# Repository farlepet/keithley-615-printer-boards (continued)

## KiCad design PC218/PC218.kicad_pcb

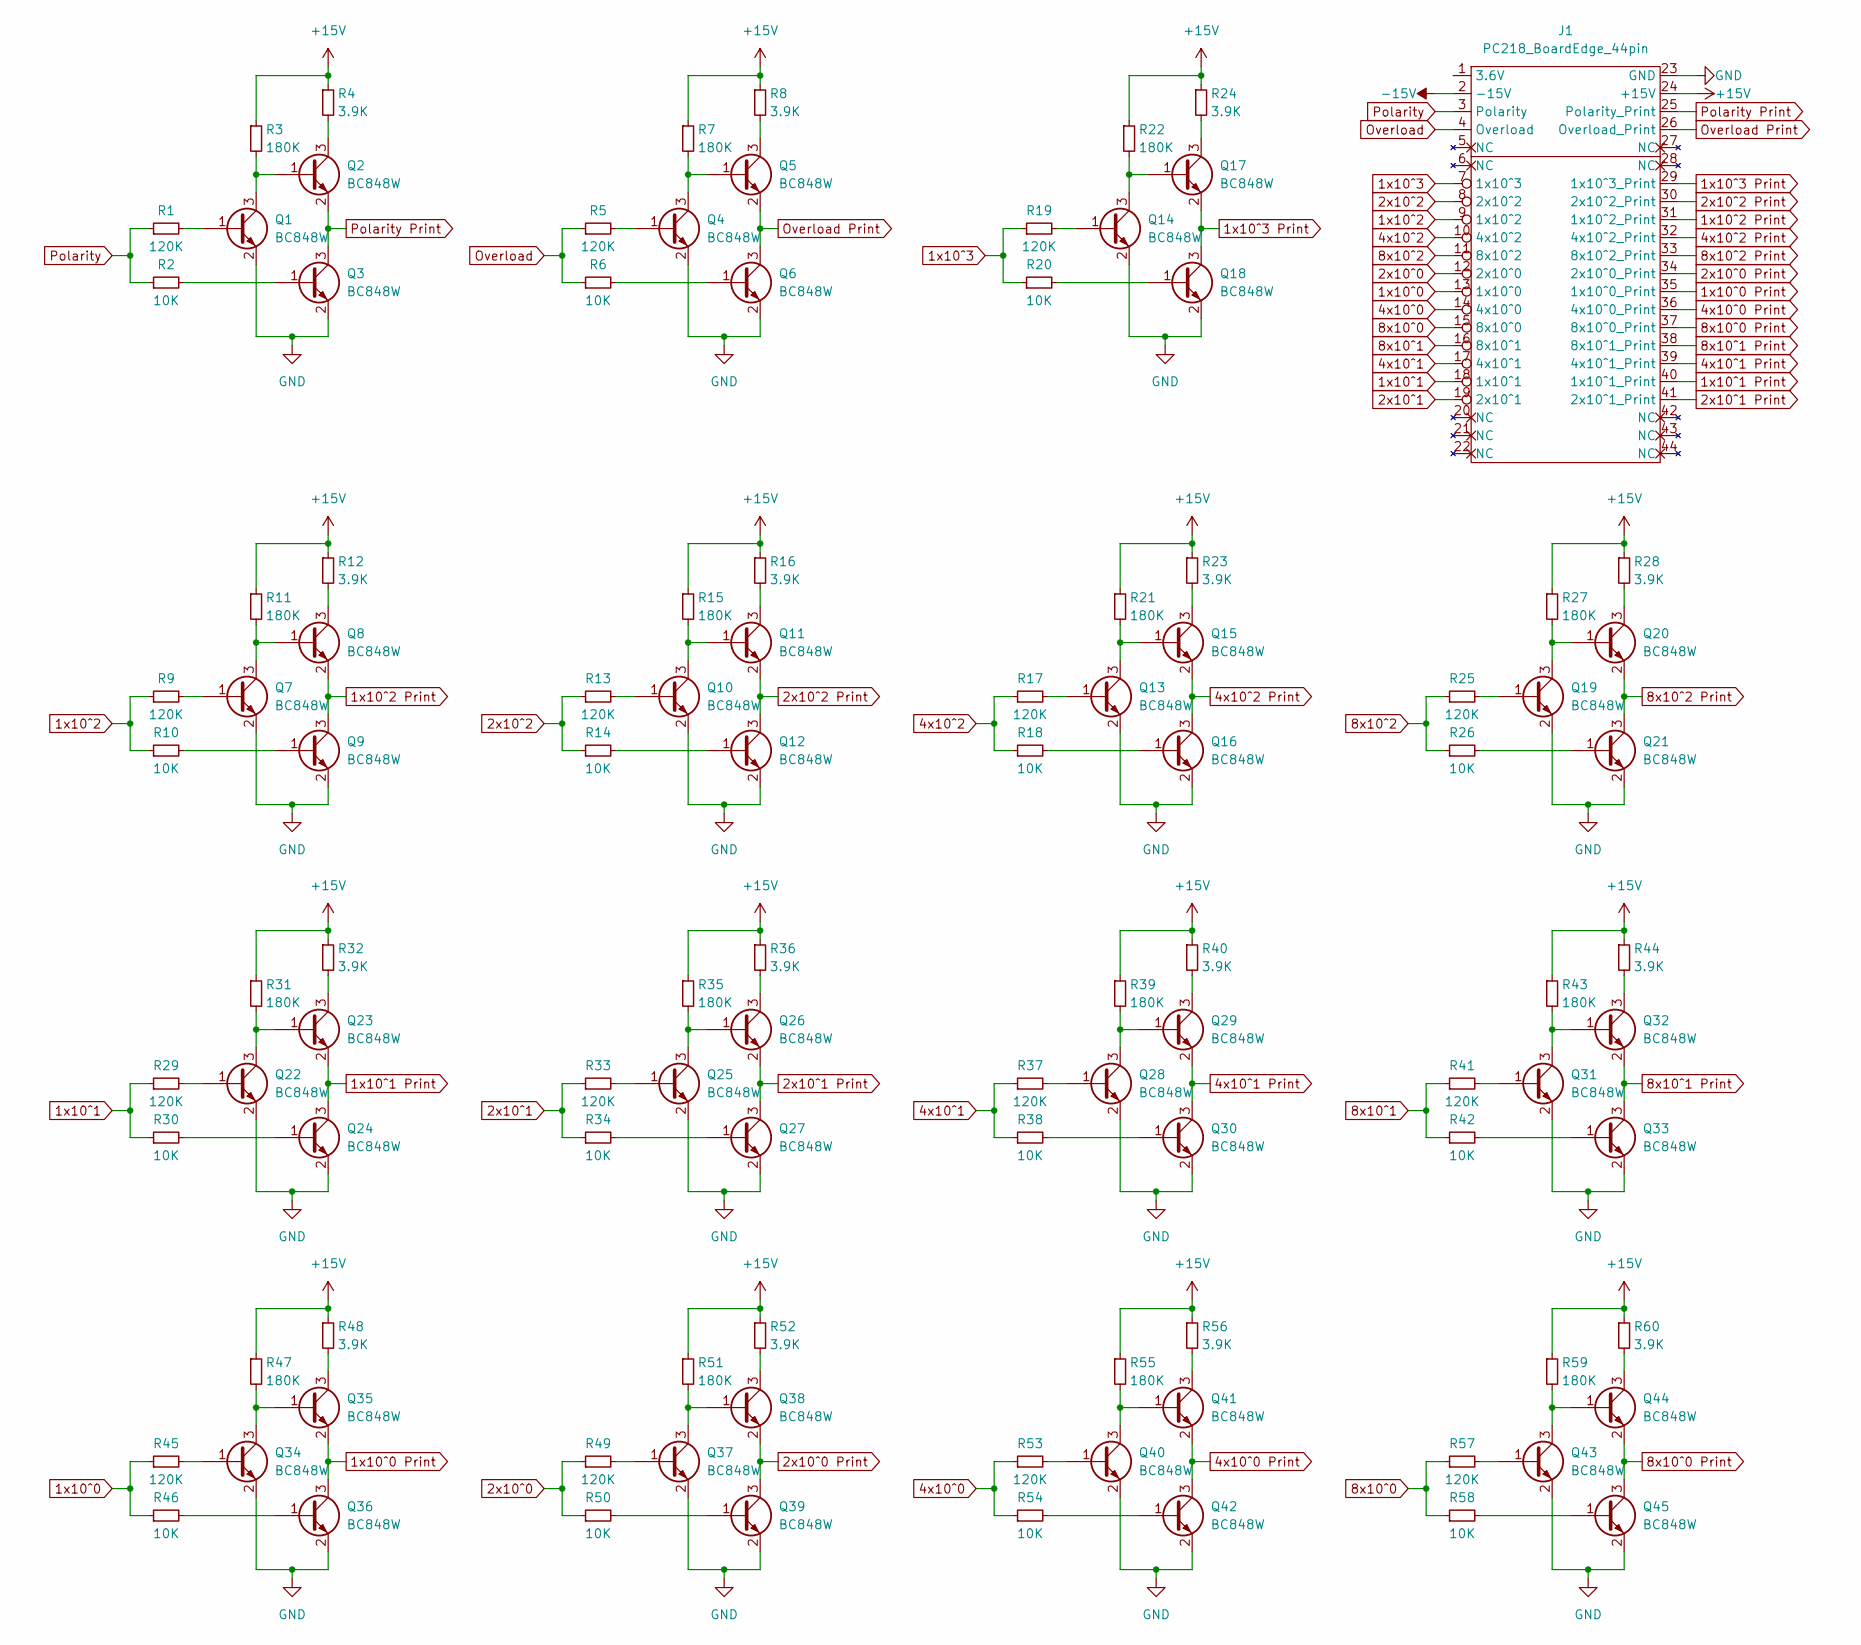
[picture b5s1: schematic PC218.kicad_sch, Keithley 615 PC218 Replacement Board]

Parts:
J1: PC218_BoardEdge_44pin; PC218_Edge_Connector
Q1, Q2, Q3, Q4, Q5, Q6, Q7, Q8, Q9, Q10, Q11, Q12, Q13, Q14, Q15, Q16, Q17, Q18, Q19, Q20, Q21, Q22, Q23, Q24, Q25, Q26, Q27, Q28, Q29, Q30, Q31, Q32, Q33, Q34, Q35, Q36, Q37, Q38, Q39, Q40, Q41, Q42, Q43, Q44, Q45: BC848W; SOT-323_SC-70
R1, R5, R9, R13, R17, R19, R25, R29, R33, R37, R41, R45, R49, R53, R57: 120K; R_0603_1608Metric
R2, R6, R10, R14, R18, R20, R26, R30, R34, R38, R42, R46, R50, R54, R58: 10K; R_0603_1608Metric
R3, R7, R11, R15, R21, R22, R27, R31, R35, R39, R43, R47, R51, R55, R59: 180K; R_0603_1608Metric
R4, R8, R12, R16, R23, R24, R28, R32, R36, R40, R44, R48, R52, R56, R60: 3.9K; R_0603_1608Metric

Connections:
1x10^0: J1.13 (1x10^0), R45.1, R46.1
1x10^0 Print: J1.35 (1x10^0_Print), Q35.2 (E), Q36.3 (C)
1x10^1: J1.18 (1x10^1), R29.1, R30.1
1x10^1 Print: J1.40 (1x10^1_Print), Q23.2 (E), Q24.3 (C)
1x10^2: J1.9 (1x10^2), R9.1, R10.1
1x10^2 Print: J1.31 (1x10^2_Print), Q8.2 (E), Q9.3 (C)
1x10^3: J1.7 (1x10^3), R19.1, R20.1
1x10^3 Print: J1.29 (1x10^3_Print), Q17.2 (E), Q18.3 (C)
2x10^0: J1.12 (2x10^0), R49.1, R50.1
2x10^0 Print: J1.34 (2x10^0_Print), Q38.2 (E), Q39.3 (C)
2x10^1: J1.19 (2x10^1), R33.1, R34.1
2x10^1 Print: J1.41 (2x10^1_Print), Q26.2 (E), Q27.3 (C)
2x10^2: J1.8 (2x10^2), R13.1, R14.1
2x10^2 Print: J1.30 (2x10^2_Print), Q11.2 (E), Q12.3 (C)
4x10^0: J1.14 (4x10^0), R53.1, R54.1
4x10^0 Print: J1.36 (4x10^0_Print), Q41.2 (E), Q42.3 (C)
4x10^1: J1.17 (4x10^1), R37.1, R38.1
4x10^1 Print: J1.39 (4x10^1_Print), Q29.2 (E), Q30.3 (C)
4x10^2: J1.10 (4x10^2), R17.1, R18.1
4x10^2 Print: J1.32 (4x10^2_Print), Q15.2 (E), Q16.3 (C)
8x10^0: J1.15 (8x10^0), R57.1, R58.1
8x10^0 Print: J1.37 (8x10^0_Print), Q44.2 (E), Q45.3 (C)
8x10^1: J1.16 (8x10^1), R41.1, R42.1
8x10^1 Print: J1.38 (8x10^1_Print), Q32.2 (E), Q33.3 (C)
8x10^2: J1.11 (8x10^2), R25.1, R26.1
8x10^2 Print: J1.33 (8x10^2_Print), Q20.2 (E), Q21.3 (C)
+15V: J1.24 (+15V), R3.1, R4.1, R7.1, R8.1, R11.1, R12.1, R15.1, R16.1, R21.1, R22.1, R23.1, R24.1, R27.1, R28.1, R31.1, R32.1, R35.1, R36.1, R39.1, R40.1, R43.1, R44.1, R47.1, R48.1, R51.1, R52.1, R55.1, R56.1, R59.1, R60.1
-15V: J1.2 (-15V)
GND: J1.23 (GND), Q1.2 (E), Q3.2 (E), Q4.2 (E), Q6.2 (E), Q7.2 (E), Q9.2 (E), Q10.2 (E), Q12.2 (E), Q13.2 (E), Q14.2 (E), Q16.2 (E), Q18.2 (E), Q19.2 (E), Q21.2 (E), Q22.2 (E), Q24.2 (E), Q25.2 (E), Q27.2 (E), Q28.2 (E), Q30.2 (E), Q31.2 (E), Q33.2 (E), Q34.2 (E), Q36.2 (E), Q37.2 (E), Q39.2 (E), Q40.2 (E), Q42.2 (E), Q43.2 (E), Q45.2 (E)
unnamed: Q1.1 (B), R1.2
unnamed: Q1.3 (C), Q2.1 (B), R3.2
unnamed: Q2.3 (C), R4.2
unnamed: Q3.1 (B), R2.2
unnamed: Q4.1 (B), R5.2
unnamed: Q4.3 (C), Q5.1 (B), R7.2
unnamed: Q5.3 (C), R8.2
unnamed: Q6.1 (B), R6.2
unnamed: Q7.1 (B), R9.2
unnamed: Q7.3 (C), Q8.1 (B), R11.2
unnamed: Q8.3 (C), R12.2
unnamed: Q9.1 (B), R10.2
unnamed: Q10.1 (B), R13.2
unnamed: Q10.3 (C), Q11.1 (B), R15.2
unnamed: Q11.3 (C), R16.2
unnamed: Q12.1 (B), R14.2
unnamed: Q13.1 (B), R17.2
unnamed: Q13.3 (C), Q15.1 (B), R21.2
unnamed: Q14.1 (B), R19.2
unnamed: Q14.3 (C), Q17.1 (B), R22.2
unnamed: Q15.3 (C), R23.2
unnamed: Q16.1 (B), R18.2
unnamed: Q17.3 (C), R24.2
unnamed: Q18.1 (B), R20.2
unnamed: Q19.1 (B), R25.2
unnamed: Q19.3 (C), Q20.1 (B), R27.2
unnamed: Q20.3 (C), R28.2
unnamed: Q21.1 (B), R26.2
unnamed: Q22.1 (B), R29.2
unnamed: Q22.3 (C), Q23.1 (B), R31.2
unnamed: Q23.3 (C), R32.2
unnamed: Q24.1 (B), R30.2
unnamed: Q25.1 (B), R33.2
unnamed: Q25.3 (C), Q26.1 (B), R35.2
unnamed: Q26.3 (C), R36.2
unnamed: Q27.1 (B), R34.2
unnamed: Q28.1 (B), R37.2
unnamed: Q28.3 (C), Q29.1 (B), R39.2
unnamed: Q29.3 (C), R40.2
unnamed: Q30.1 (B), R38.2
unnamed: Q31.1 (B), R41.2
unnamed: Q31.3 (C), Q32.1 (B), R43.2
unnamed: Q32.3 (C), R44.2
unnamed: Q33.1 (B), R42.2
unnamed: Q34.1 (B), R45.2
unnamed: Q34.3 (C), Q35.1 (B), R47.2
unnamed: Q35.3 (C), R48.2
unnamed: Q36.1 (B), R46.2
unnamed: Q37.1 (B), R49.2
unnamed: Q37.3 (C), Q38.1 (B), R51.2
unnamed: Q38.3 (C), R52.2
unnamed: Q39.1 (B), R50.2
unnamed: Q40.1 (B), R53.2
unnamed: Q40.3 (C), Q41.1 (B), R55.2
unnamed: Q41.3 (C), R56.2
unnamed: Q42.1 (B), R54.2
unnamed: Q43.1 (B), R57.2
unnamed: Q43.3 (C), Q44.1 (B), R59.2
unnamed: Q44.3 (C), R60.2
unnamed: Q45.1 (B), R58.2
Overload: J1.4 (Overload), R5.1, R6.1
Overload Print: J1.26 (Overload_Print), Q5.2 (E), Q6.3 (C)
Polarity: J1.3 (Polarity), R1.1, R2.1
Polarity Print: J1.25 (Polarity_Print), Q2.2 (E), Q3.3 (C)

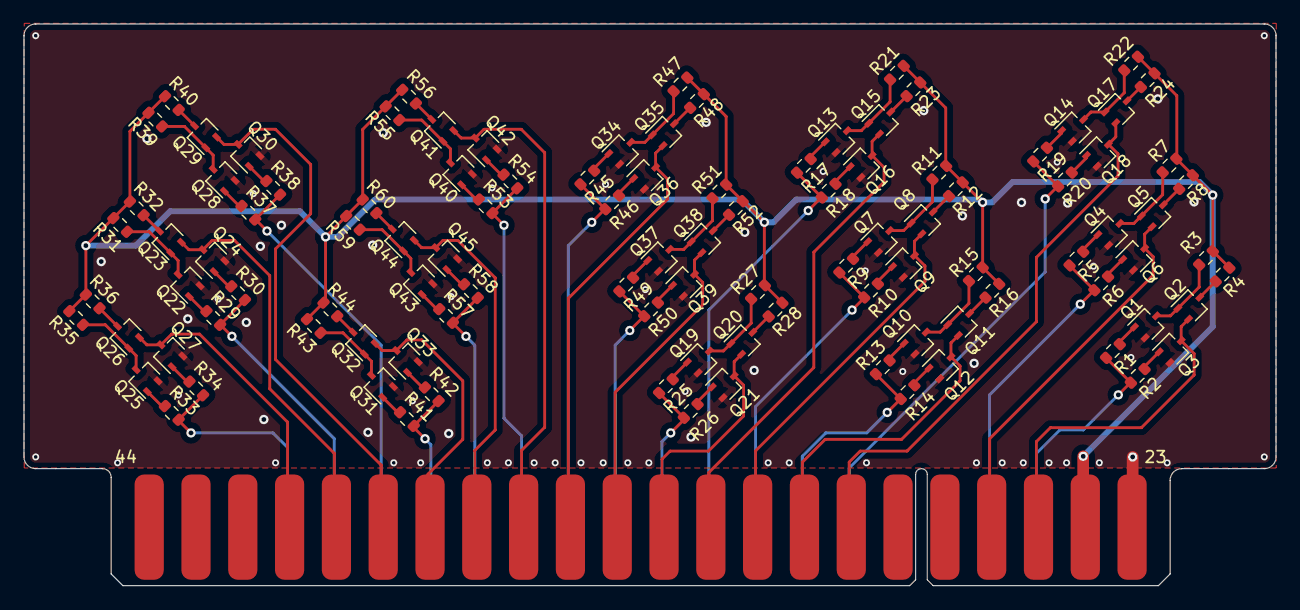
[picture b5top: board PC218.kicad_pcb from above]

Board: 2 copper layers, 107.0 x 48.0 mm, 106 parts (0 on the bottom side), 92 nets.

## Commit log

2022-12-30 Initial prototype for PC218
2022-12-30 Add readme
2022-12-31 Add new version of PC218 using less components.
2023-01-11 Add images of boards, update README, add LICENSE
2023-01-11 PC218 Rev 1.1
    Fixed disconnected ground plane resulting in two buffers being unpowered
    Moved silkscreen to front, add OSHW logo
    Move symbols and footprints to shared library
    Update edge connector footprint to use a more sane orientation
2023-01-11 Use transparent images
2023-01-11 Fix rear image of PC218 V2.0
2023-01-11 Rename project files for PC218 Rev 2
2023-01-11 PC218 Rev 2.1
2023-01-12 PC209: Initial design for pulse generator
2023-01-16 PC209: Initial layout for pulse generator sections
2023-01-16 Fix name for SnapEDA license
2023-01-16 PC209: Initial board routing
2023-01-16 PC209: Rev 1.0
2023-01-17 PC218v2: Rev 2.2
    Matched form factor of new PC209 board
    Added power test points
2023-01-17 PC209: Fix silkscreen error, backannotate to schematic.
2023-01-18 50PinTestBoard: Start work on board to test all connections of the 50-pin connector.
2023-01-19 50PinTestBoard: Rev 1.0
2023-01-21 50PinTestBoard: Rev 1.1
    Made screw holes for connector foot print plated through-holes.
2023-01-25 InterfaceBoard: Rough in Ethernet, USB, and 50-pin
2023-01-25 Add PDFs of schematics and board layout.
2023-01-26 InterfaceBoard: Add RS-232/DE-9
2023-01-28 InterfaceBoard: Add STM32G0B1RET
2023-02-01 PC209: Fix position of -15 V and +3.6 V on card edge
    Update component values
    Make library path relative
2023-02-01 PC218: Make library path relative
2023-02-01 PC218v2: Make library path relative
2023-02-01 InterfaceBoard: Make library paths relative
2023-02-01 PC209: Add simulation document
2023-02-01 50PinTestBoard: Make library paths relative
2023-02-01 PC209: Add BOM
2023-02-04 50PinTestBoard: Fix year
2023-02-05 Fix 50-pin connector pin numbering.
2023-02-05 50PinTestBoard: Rev 1.2
    Fix orientation of connector footprint
    - Moved connector to bottom of board to avoid re-routing entire board.
    Update resistor value(s).
    Add Digi-Key links for parts.
2023-02-05 50PinTestBoard: Add BOM
2023-02-05 InterfaceBoard: Update connector footprint
2023-02-22 InterfaceBoard: Add 3.3 V regulater, test points.
2023-02-22 InterfaceBoard: MAX232 -> MAX3232
2023-02-24 InterfaceBoard: Routed Ethernet
2023-02-26 InterfaceBoard: Routed some digital interfaces to MCU
2023-03-01 InterfaceBoard: Place and route buttons and LEDs.
2023-03-01 InterfaceBoard: Swap trigger and reset buttons
2023-03-02 InterfaceBoard: Route MCU USB
2023-03-03 InterfaceBoard: Fully route board.
2023-03-03 InterfaceBoard: Geographical reannotation.
2023-03-04 InterfaceBoard: Rev 1.0
2023-03-04 InterfaceBoard: Add BOM
2023-03-04 InterfaceBoard: Add PCB/SCH PDFs.
2023-03-31 Update board images
2023-11-03 DNI R31 from PC209
    This resistor prevents sensitivity 2x10^0 from hitting the proper logic levels.
